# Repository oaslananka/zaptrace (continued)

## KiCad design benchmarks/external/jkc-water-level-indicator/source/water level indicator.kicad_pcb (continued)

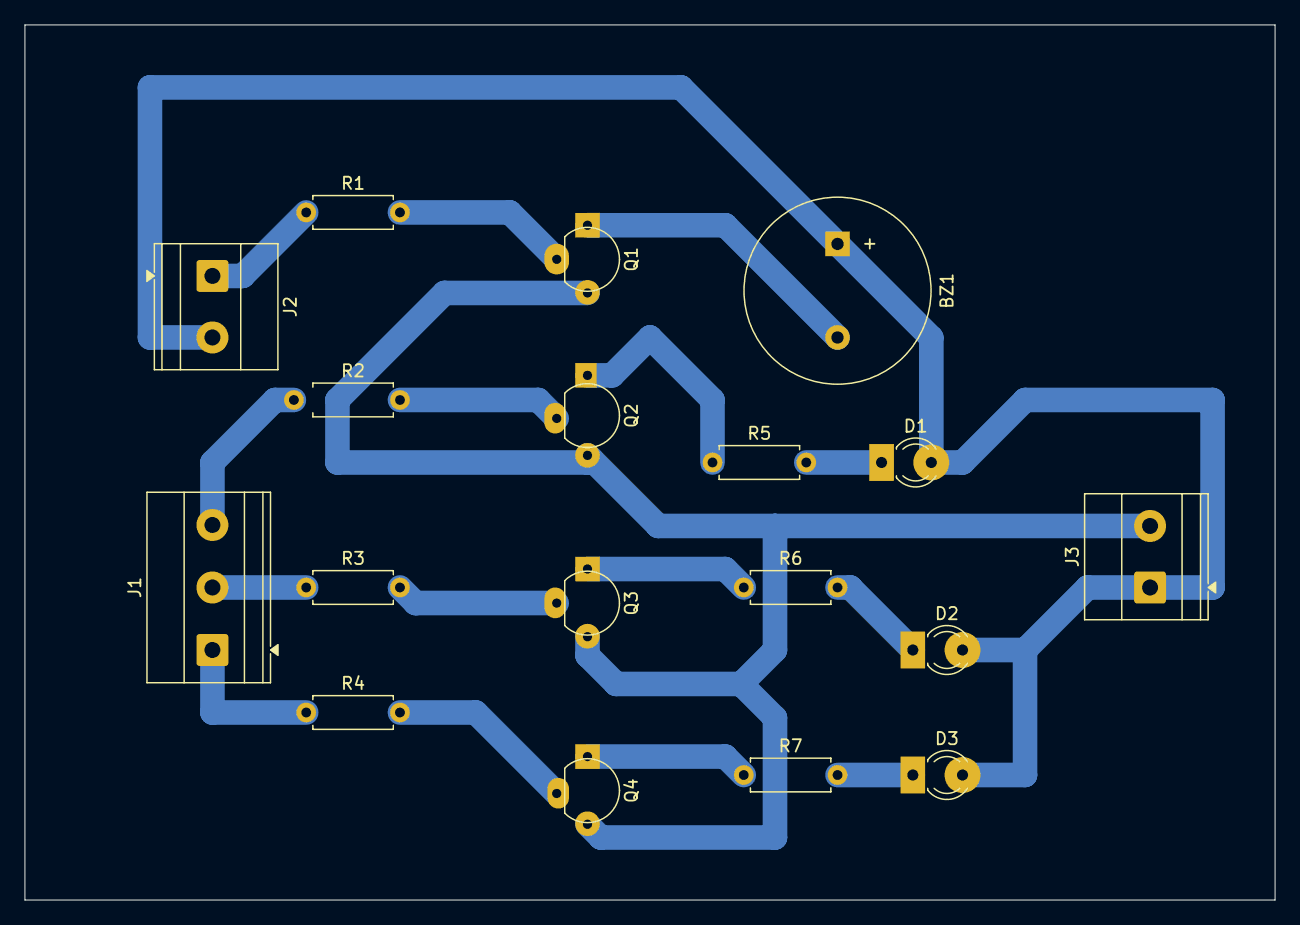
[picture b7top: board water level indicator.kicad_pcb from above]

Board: 2 copper layers, 101.6 x 71.1 mm, 18 parts (0 on the bottom side), 17 nets.

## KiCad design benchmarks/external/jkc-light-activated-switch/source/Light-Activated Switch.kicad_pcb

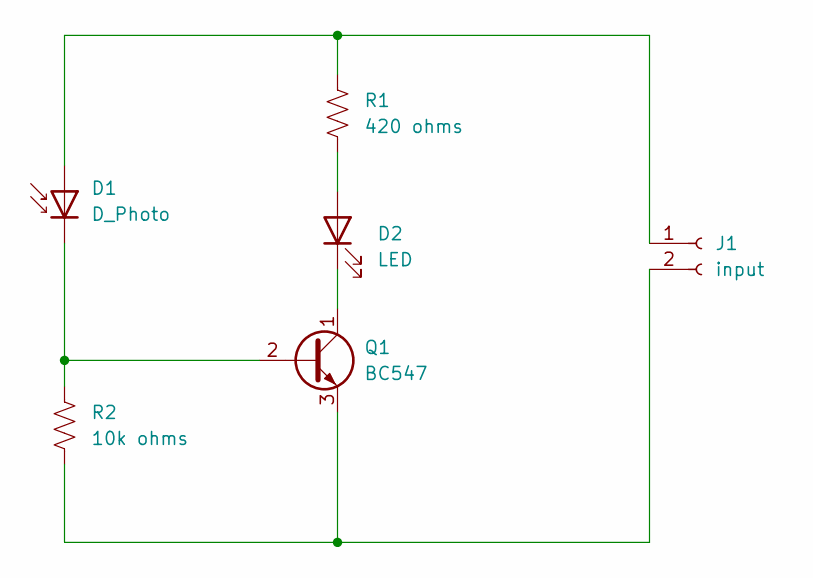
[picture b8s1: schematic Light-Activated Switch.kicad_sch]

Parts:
D1: D_Photo; LED_D5.0mm_IRBlack
D2: LED; LED_D5.0mm
J1: input; TerminalBlock_Phoenix_MKDS-1,5-2_1x02_P5.00mm_Horizontal
Q1: BC547; TO-92_Inline
R1: 420 ohms; R_Axial_DIN0207_L6.3mm_D2.5mm_P10.16mm_Horizontal
R2: 10k ohms; R_Axial_DIN0207_L6.3mm_D2.5mm_P10.16mm_Horizontal

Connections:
unnamed: D1.2 (A), J1.1, R1.1
unnamed: D1.1 (K), Q1.2 (B), R2.1
unnamed: D2.2 (A), R1.2
unnamed: D2.1 (K), Q1.1 (C)
unnamed: J1.2, Q1.3 (E), R2.2

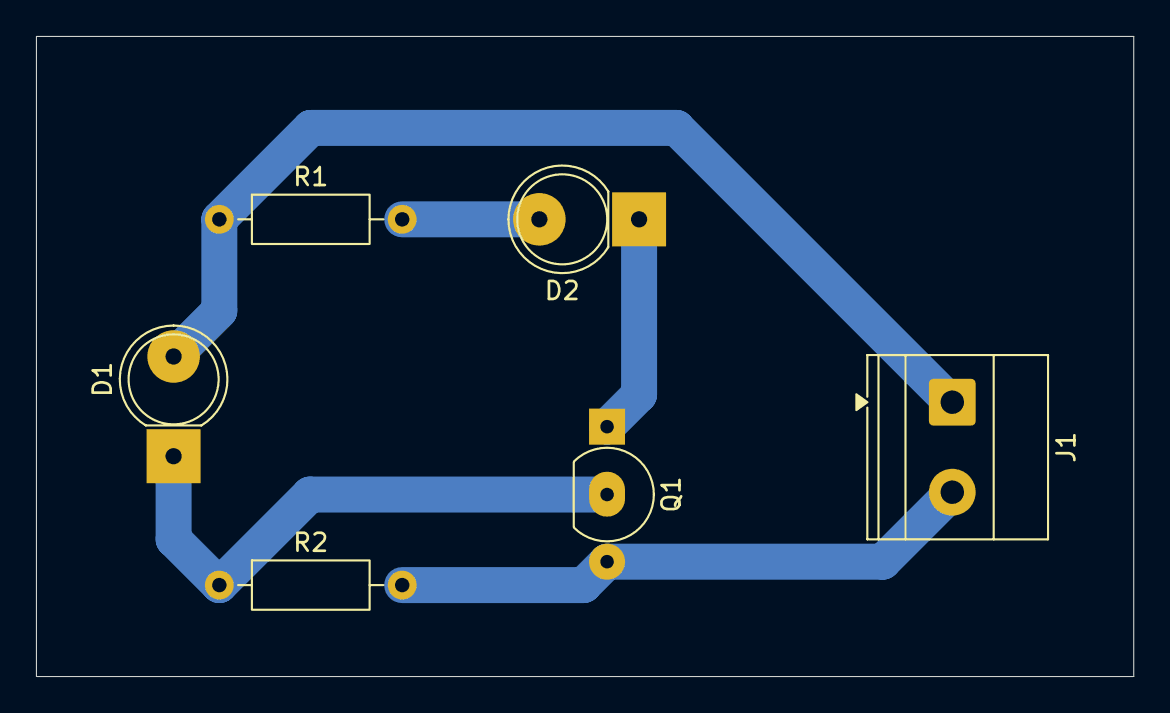
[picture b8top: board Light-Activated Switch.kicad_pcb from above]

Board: 2 copper layers, 61.0 x 35.6 mm, 6 parts (0 on the bottom side), 5 nets.
